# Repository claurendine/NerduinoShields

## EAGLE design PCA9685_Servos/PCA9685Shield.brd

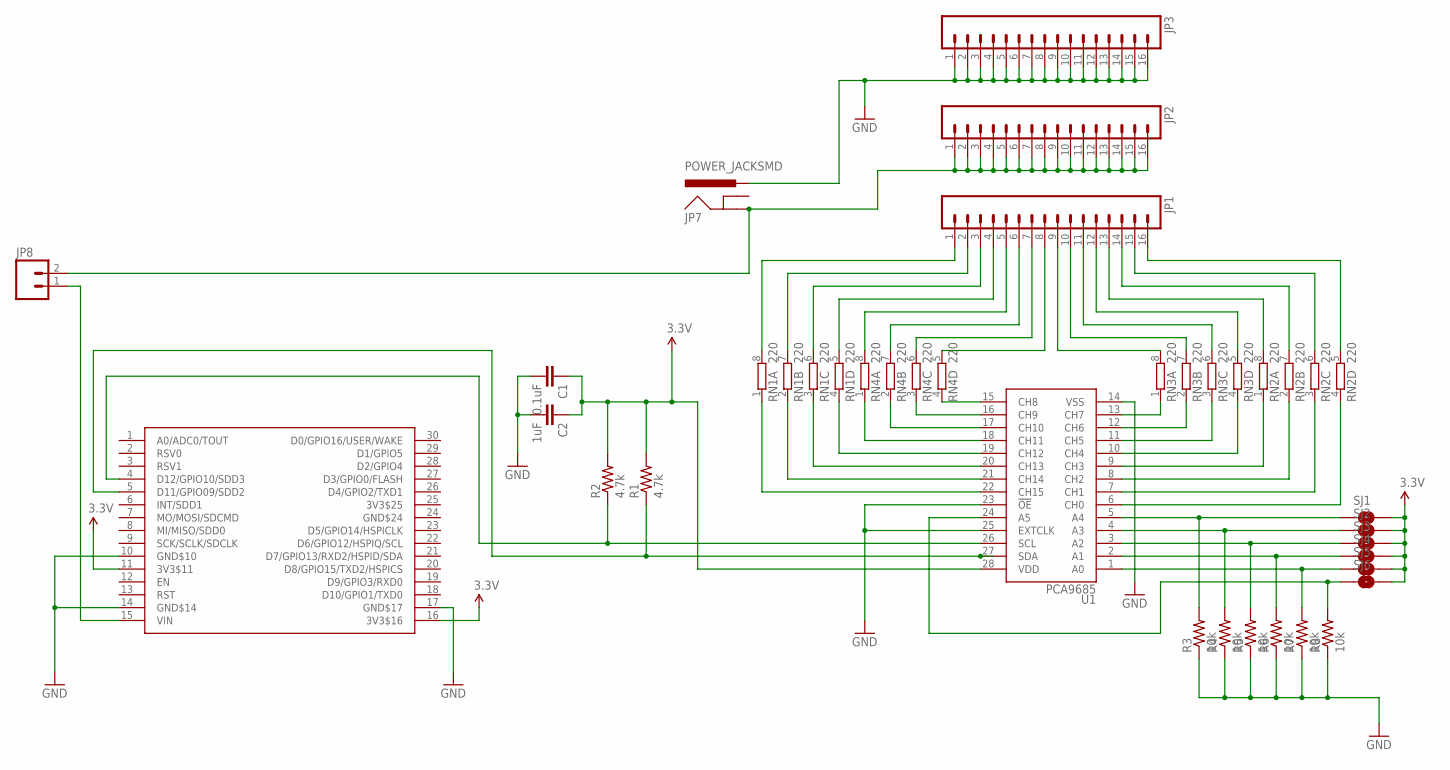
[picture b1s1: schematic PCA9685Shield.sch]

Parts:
C1: 0.1uF; 0402-CAP
C2: 1uF; 0402-CAP
JP1, JP2, JP3: M161X16_NO_SILK; 1X16_NO_SILK
JP7: POWER_JACKSMD; POWER_JACK_SMD
JP8: M021X02_NO_SILK; 1X02_NO_SILK
R1, R2: 4.7k; 0402-RES
R3, R4, R5, R6, R7, R8: 10k; 0402-RES
RN1, RN2, RN3, RN4: 220; EXBS8V
SJ1, SJ2, SJ3, SJ4, SJ5, SJ6: SOLDERJUMPERNO; SJ_2S-NO
U1: PCA9685; TSSOP-28_4MM
U$1: NERDSHIELD; NERDUINO_STACK

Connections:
3.3V: C1.1, C2.1, R1.2, R2.2, SJ1.2, SJ2.2, SJ3.2, SJ4.2, SJ5.2, SJ6.2, U1.28 (VDD), U$1.11 (3V3$11), U$1.16 (3V3$16)
GND: C1.2, C2.2, JP3.1, JP3.2, JP3.3, JP3.4, JP3.5, JP3.6, JP3.7, JP3.8, JP3.9, JP3.10, JP3.11, JP3.12, JP3.13, JP3.14, JP3.15, JP3.16, JP7.VIN0 (PWR), R3.1, R4.1, R5.1, R6.1, R7.1, R8.1, U1.14 (VSS), U1.23 (!OE), U1.25 (EXTCLK), U$1.10 (GND$10), U$1.14 (GND$14), U$1.17 (GND$17)
unnamed: JP8.1, U$1.15 (VIN)
unnamed: R1.1, U1.27 (SDA), U$1.5 (D11/GPIO09/SDD2)
unnamed: R7.2, SJ5.1, U1.1 (A0)
unnamed: R6.2, SJ4.1, U1.2 (A1)
unnamed: R5.2, SJ3.1, U1.3 (A2)
unnamed: R4.2, SJ2.1, U1.4 (A3)
unnamed: R2.1, U1.26 (SCL), U$1.4 (D12/GPIO10/SDD3)
unnamed: R8.2, SJ6.1, U1.24 (A5)
unnamed: RN2.4 (1), U1.6 (CH0)
unnamed: JP1.15, RN2.6 (2)
unnamed: JP1.14, RN2.7 (2)
unnamed: JP1.13, RN2.8 (2)
unnamed: JP1.12, RN3.5 (2)
unnamed: JP1.11, RN3.6 (2)
unnamed: JP1.10, RN3.7 (2)
unnamed: JP1.9, RN3.8 (2)
unnamed: JP1.8, RN4.5 (2)
unnamed: JP1.7, RN4.6 (2)
unnamed: JP1.6, RN4.7 (2)
unnamed: JP1.5, RN4.8 (2)
unnamed: JP1.4, RN1.5 (2)
unnamed: JP1.3, RN1.6 (2)
unnamed: RN1.2 (1), U1.21 (CH14)
unnamed: RN1.1, U1.22 (CH15)
unnamed: JP2.1, JP2.2, JP2.3, JP2.4, JP2.5, JP2.6, JP2.7, JP2.8, JP2.9, JP2.10, JP2.11, JP2.12, JP2.13, JP2.14, JP2.15, JP2.16, JP7.P$4 (GND), JP8.2
unnamed: JP1.2, RN1.7 (2)
unnamed: JP1.1, RN1.8 (2)
unnamed: RN1.3 (1), U1.20 (CH13)
unnamed: RN1.4 (1), U1.19 (CH12)
unnamed: RN4.1, U1.18 (CH11)
unnamed: RN4.2 (1), U1.17 (CH10)
unnamed: RN4.3 (1), U1.16 (CH9)
unnamed: RN4.4 (1), U1.15 (CH8)
unnamed: RN3.1, U1.13 (CH7)
unnamed: RN3.2 (1), U1.12 (CH6)
unnamed: RN3.3 (1), U1.11 (CH5)
unnamed: RN3.4 (1), U1.10 (CH4)
unnamed: RN2.1, U1.9 (CH3)
unnamed: RN2.2 (1), U1.8 (CH2)
unnamed: RN2.3 (1), U1.7 (CH1)
unnamed: JP1.16, RN2.5 (2)
unnamed: R3.2, SJ1.1, U1.5 (A4)

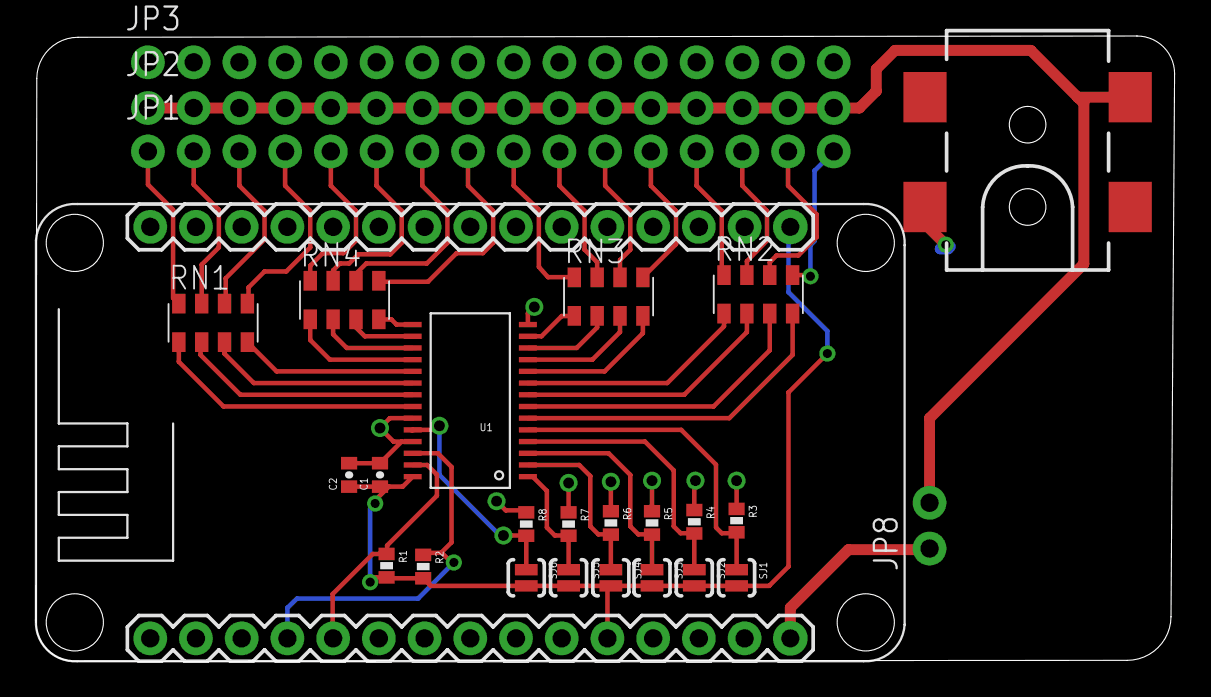
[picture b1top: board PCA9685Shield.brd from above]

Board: 2 copper layers, 63.3 x 34.7 mm, 27 parts (0 on the bottom side), 44 nets.

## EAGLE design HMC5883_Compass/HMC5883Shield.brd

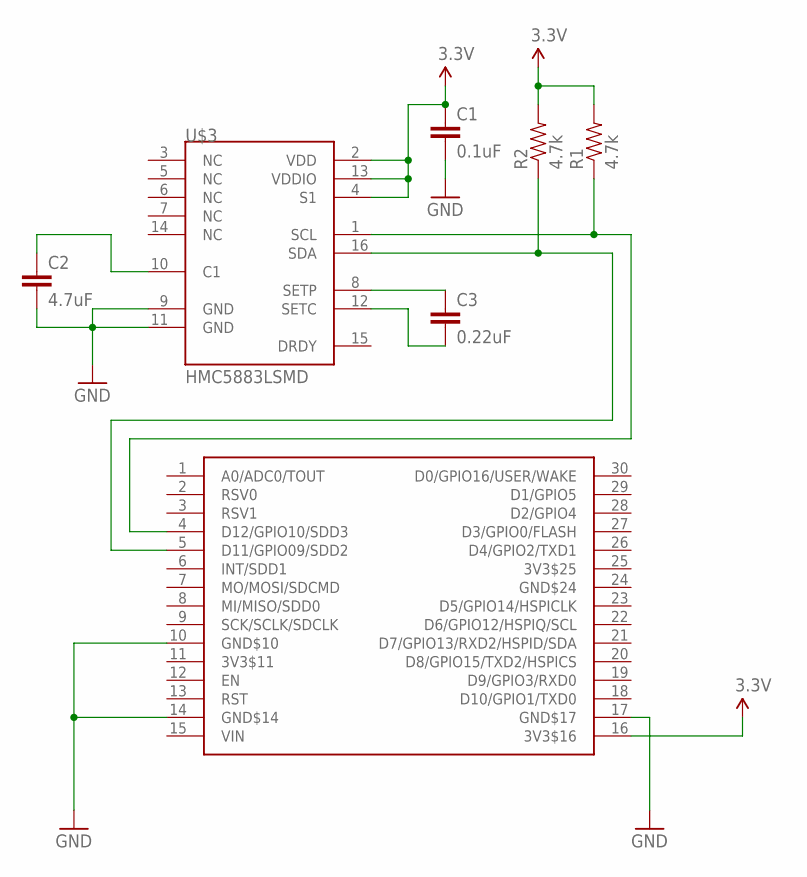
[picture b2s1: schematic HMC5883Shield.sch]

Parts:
C1: 0.1uF; 0402-CAP
C2: 4.7uF; 0402-CAP
C3: 0.22uF; 0402-CAP
R1, R2: 4.7k; 0402-RES
U$1: NERDSHIELD; NERDUINO_STACK
U$3: HMC5883LSMD; 16LPCC

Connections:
3.3V: C1.1, R1.2, R2.2, U$1.16 (3V3$16), U$3.2 (VDD), U$3.4 (S1), U$3.13 (VDDIO)
GND: C1.2, C2.2, U$1.10 (GND$10), U$1.14 (GND$14), U$1.17 (GND$17), U$3.9 (GND), U$3.11 (GND)
unnamed: C2.1, U$3.10 (C1)
unnamed: R2.1, U$1.5 (D11/GPIO09/SDD2), U$3.16 (SDA)
unnamed: R1.1, U$1.4 (D12/GPIO10/SDD3), U$3.1 (SCL)
unnamed: C3.1, U$3.8 (SETP)
unnamed: C3.2, U$3.12 (SETC)

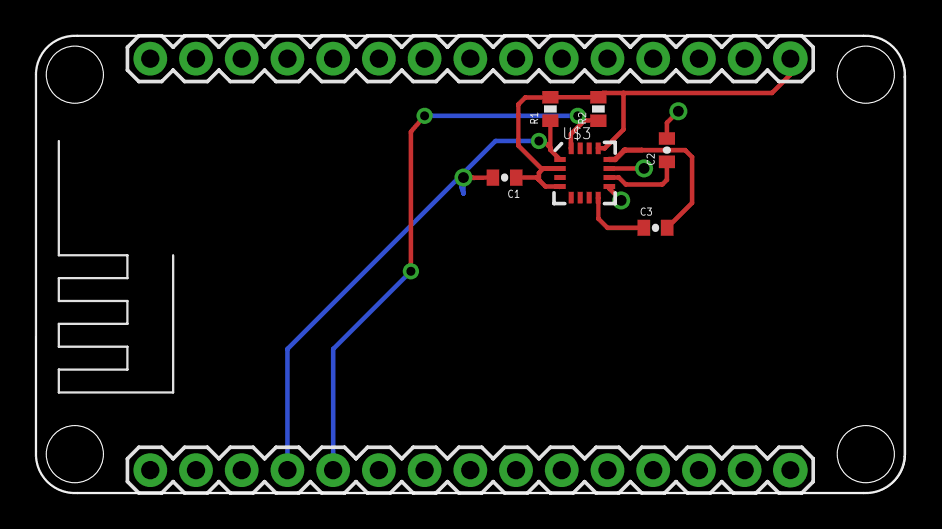
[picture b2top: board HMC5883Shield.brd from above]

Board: 2 copper layers, 48.3 x 25.4 mm, 7 parts (0 on the bottom side), 7 nets.

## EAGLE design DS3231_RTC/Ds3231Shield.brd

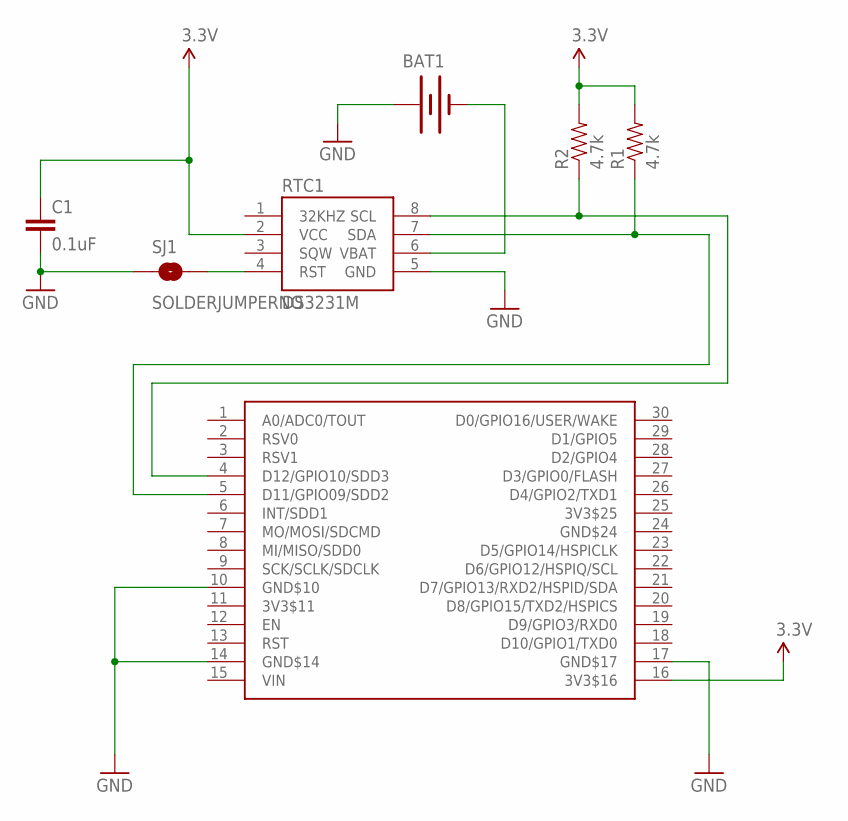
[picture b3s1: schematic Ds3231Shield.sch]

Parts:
BAT1: BATTERY12MM; BATTCON_12MM
C1: 0.1uF; 0402-CAP
R1, R2: 4.7k; 0402-RES
RTC1: DS3231M; SOIC8
SJ1: SOLDERJUMPERNO; SJ_2S-NO
U$1: NERDSHIELD; NERDUINO_STACK

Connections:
3.3V: C1.1, R1.2, R2.2, RTC1.2 (VCC), U$1.16 (3V3$16)
GND: BAT1.PWR@1 (+), C1.2, RTC1.5 (GND), SJ1.1, U$1.10 (GND$10), U$1.14 (GND$14), U$1.17 (GND$17)
unnamed: BAT1.GND (-), RTC1.6 (VBAT)
unnamed: R2.1, RTC1.8 (SCL), U$1.4 (D12/GPIO10/SDD3)
unnamed: R1.1, RTC1.7 (SDA), U$1.5 (D11/GPIO09/SDD2)
unnamed: RTC1.4 (RST), SJ1.2

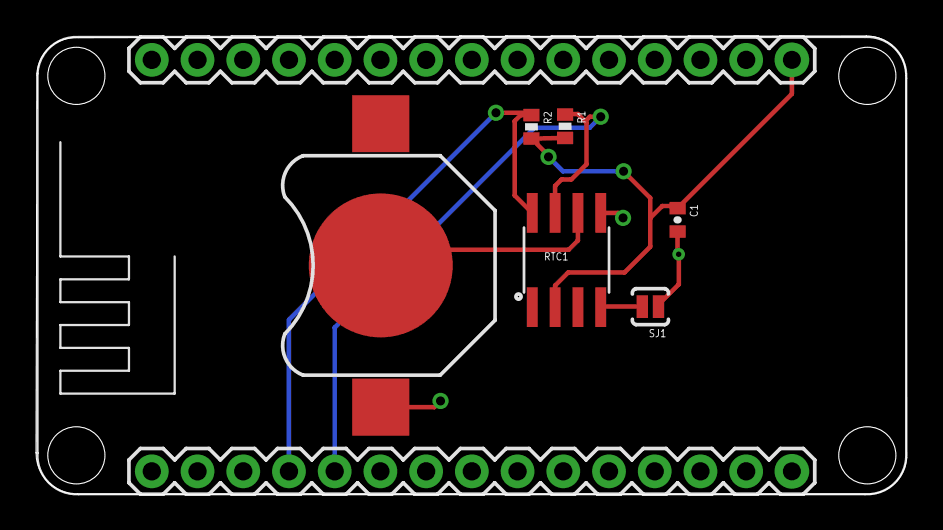
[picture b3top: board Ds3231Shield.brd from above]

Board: 2 copper layers, 48.4 x 25.5 mm, 7 parts (0 on the bottom side), 6 nets.

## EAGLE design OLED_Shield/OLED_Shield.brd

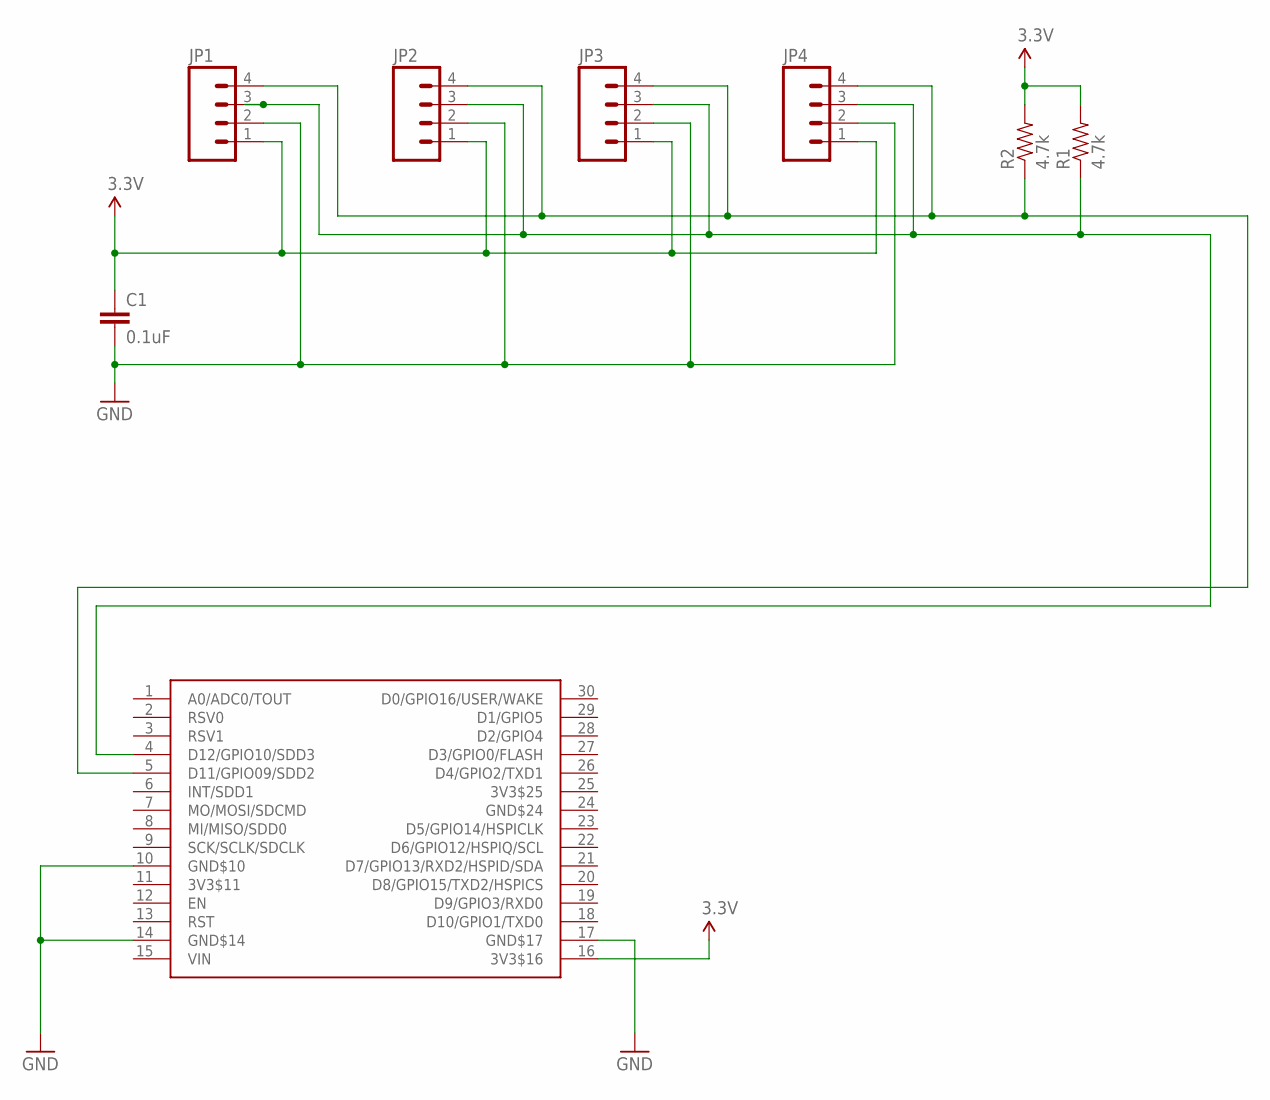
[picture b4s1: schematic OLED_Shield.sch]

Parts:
C1: 0.1uF; 0402-CAP
JP1, JP2, JP3, JP4: M041X04_NO_SILK; 1X04_NO_SILK
R1, R2: 4.7k; 0402-RES
U$1: NERDSHIELD; NERDUINO_STACK

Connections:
3.3V: C1.1, JP1.1, JP2.1, JP3.1, JP4.1, R1.2, R2.2, U$1.16 (3V3$16)
GND: C1.2, JP1.2, JP2.2, JP3.2, JP4.2, U$1.10 (GND$10), U$1.14 (GND$14), U$1.17 (GND$17)
unnamed: JP1.4, JP2.4, JP3.4, JP4.4, R2.1, U$1.5 (D11/GPIO09/SDD2)
unnamed: JP1.3, JP2.3, JP3.3, JP4.3, R1.1, U$1.4 (D12/GPIO10/SDD3)

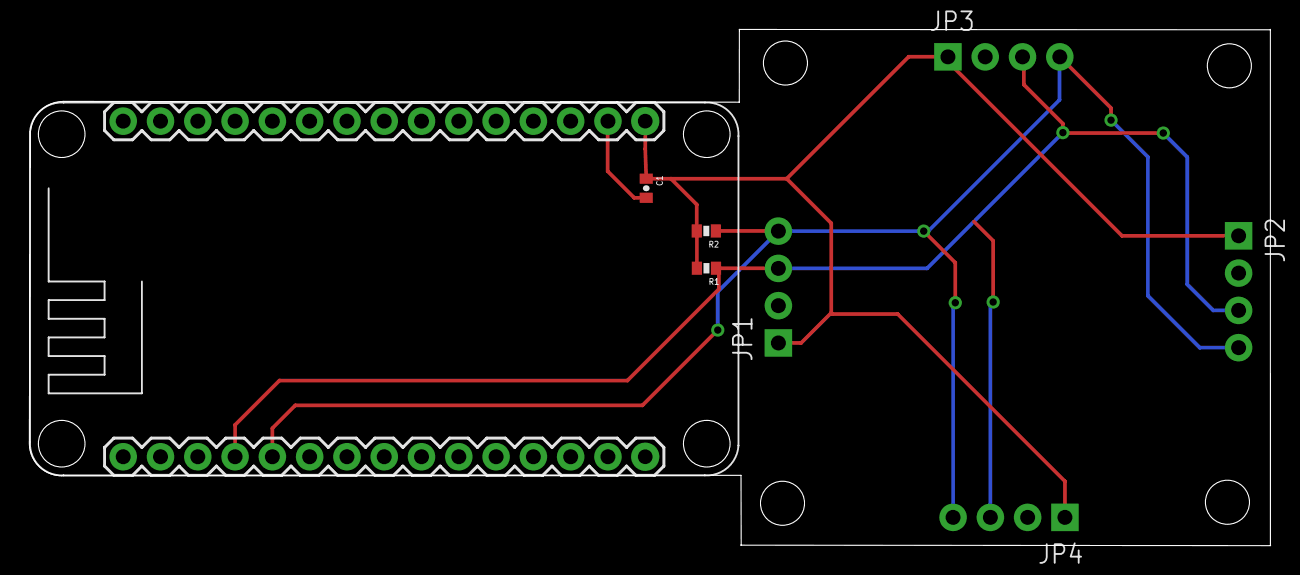
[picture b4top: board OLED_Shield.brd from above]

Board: 2 copper layers, 84.6 x 35.2 mm, 8 parts (0 on the bottom side), 4 nets.

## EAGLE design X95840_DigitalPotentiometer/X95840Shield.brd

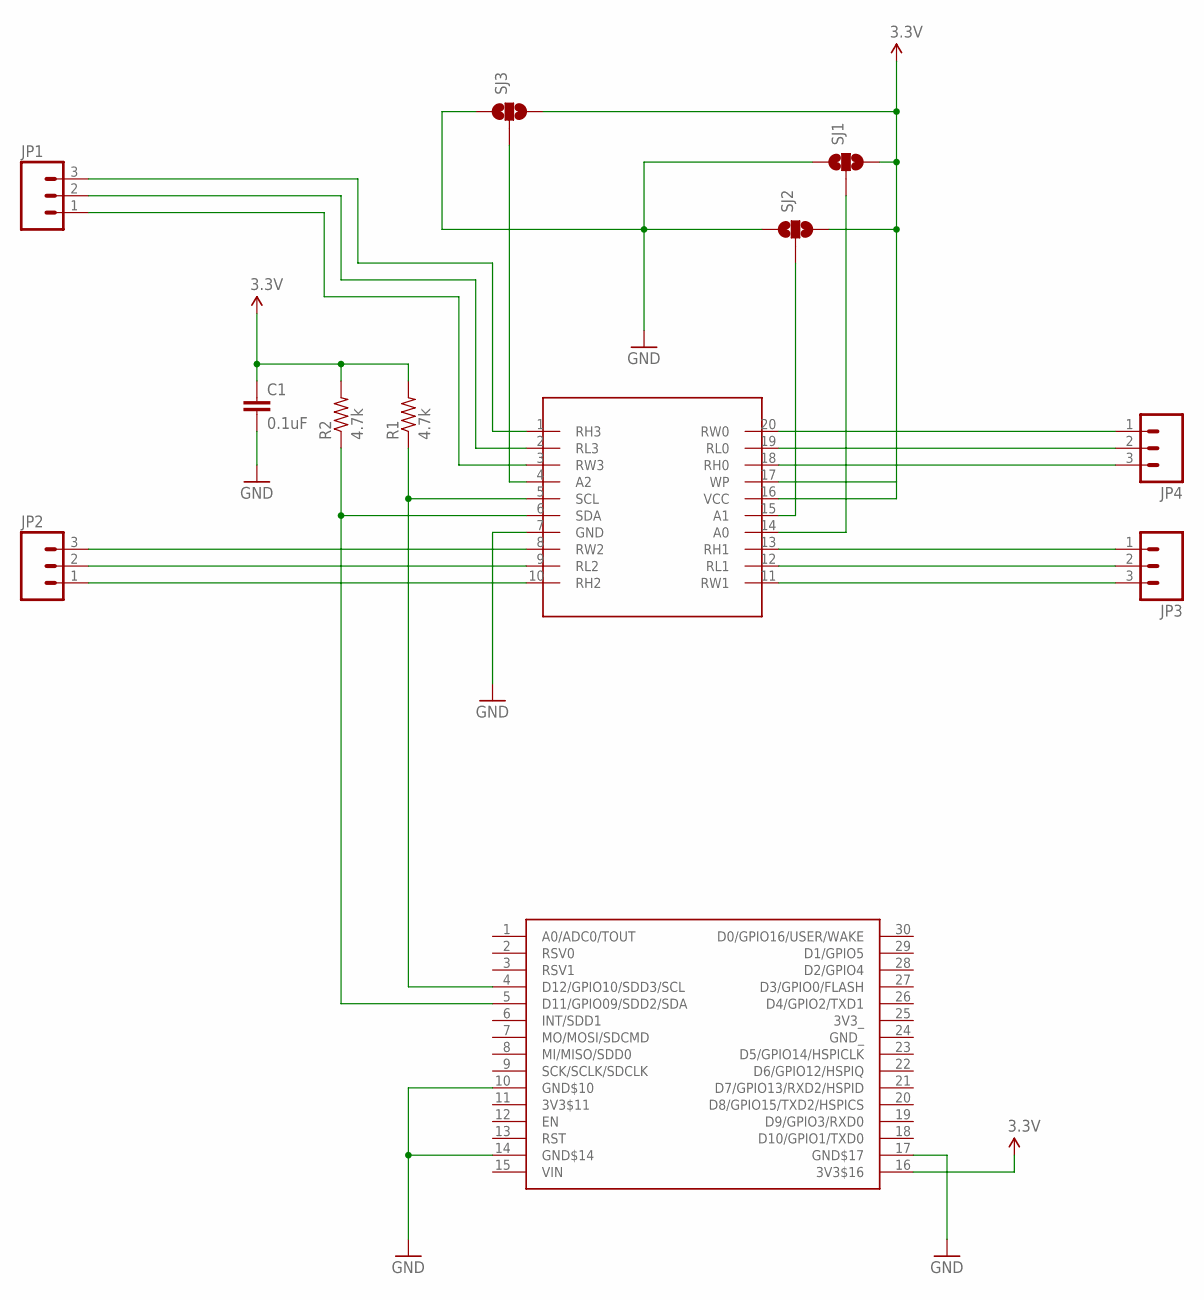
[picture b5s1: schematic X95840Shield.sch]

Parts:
C1: 0.1uF; 0402-CAP
JP1, JP2, JP3, JP4: M03SCREW; SCREWTERMINAL-3.5MM-3
R1, R2: 4.7k; 0402-RES
SJ1, SJ2, SJ3: SOLDERJUMPER_2WAYPASTE1&2; SJ_3_PASTE1&2
U$1: NERDSHIELD; NERDUINO_STACK
U$3: X95840; TSSOP20

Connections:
3.3V: C1.1, R1.2, R2.2, SJ1.3, SJ2.3, SJ3.3, U$1.16 (3V3$16), U$3.16 (VCC), U$3.17 (WP)
GND: C1.2, SJ1.1, SJ2.1, SJ3.1, U$1.10 (GND$10), U$1.14 (GND$14), U$1.17 (GND$17), U$3.7 (GND)
unnamed: SJ3.2, U$3.4 (A2)
unnamed: R2.1, U$1.5 (D11/GPIO09/SDD2/SDA), U$3.6 (SDA)
unnamed: R1.1, U$1.4 (D12/GPIO10/SDD3/SCL), U$3.5 (SCL)
unnamed: JP1.3, U$3.1 (RH3)
unnamed: JP1.2, U$3.2 (RL3)
unnamed: JP1.1, U$3.3 (RW3)
unnamed: JP2.3, U$3.8 (RW2)
unnamed: JP2.2, U$3.9 (RL2)
unnamed: SJ1.2, U$3.14 (A0)
unnamed: SJ2.2, U$3.15 (A1)
unnamed: JP2.1, U$3.10 (RH2)
unnamed: JP3.1, U$3.13 (RH1)
unnamed: JP3.2, U$3.12 (RL1)
unnamed: JP3.3, U$3.11 (RW1)
unnamed: JP4.1, U$3.20 (RW0)
unnamed: JP4.2, U$3.19 (RL0)
unnamed: JP4.3, U$3.18 (RH0)

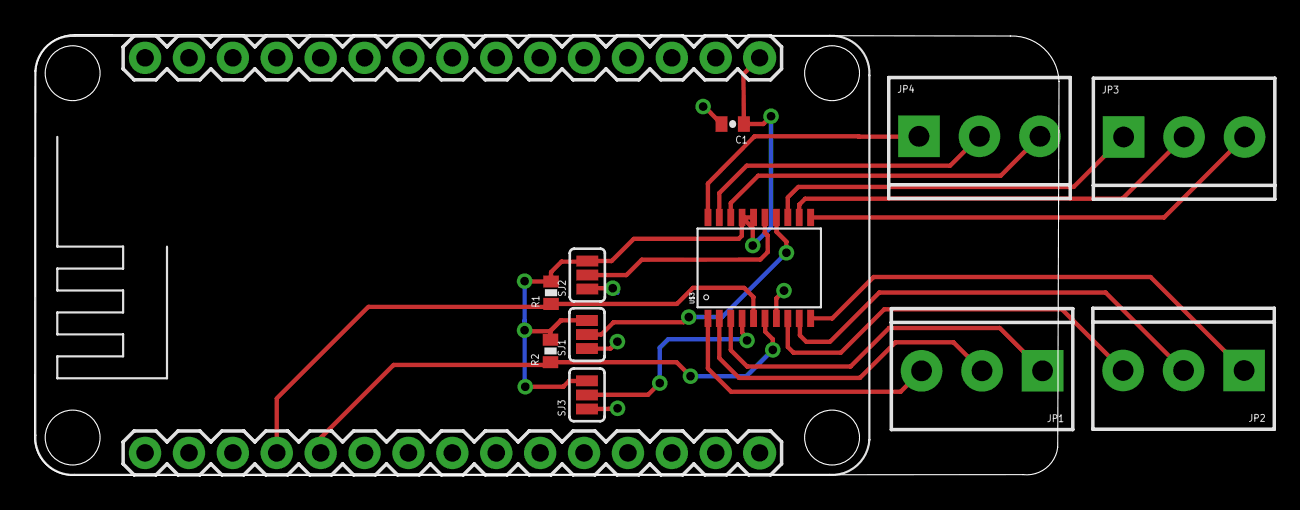
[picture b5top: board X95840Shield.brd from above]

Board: 2 copper layers, 59.3 x 25.5 mm, 12 parts (0 on the bottom side), 19 nets.

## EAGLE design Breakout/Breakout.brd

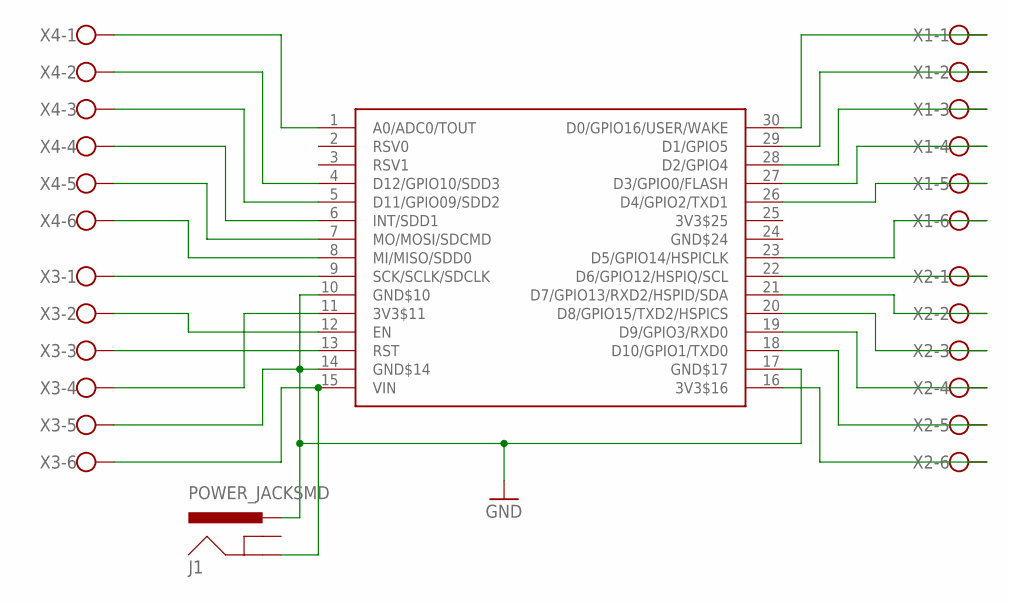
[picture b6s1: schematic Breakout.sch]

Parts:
J1: POWER_JACKSMD; POWER_JACK_SMD
U$1: NERDSHIELD; NERDUINO_STACK
X1, X2, X3, X4: W237-6

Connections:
GND: J1.VIN0 (PWR), U$1.10 (GND$10), U$1.14 (GND$14), U$1.17 (GND$17), X3.5
unnamed: U$1.16 (3V3$16), X2.6
unnamed: U$1.18 (D10/GPIO1/TXD0), X2.5
unnamed: U$1.19 (D9/GPIO3/RXD0), X2.4
unnamed: U$1.20 (D8/GPIO15/TXD2/HSPICS), X2.3
unnamed: U$1.21 (D7/GPIO13/RXD2/HSPID/SDA), X2.2
unnamed: U$1.22 (D6/GPIO12/HSPIQ/SCL), X2.1
unnamed: U$1.23 (D5/GPIO14/HSPICLK), X1.6
unnamed: U$1.26 (D4/GPIO2/TXD1), X1.5
unnamed: U$1.27 (D3/GPIO0/FLASH), X1.4
unnamed: U$1.28 (D2/GPIO4), X1.3
unnamed: U$1.29 (D1/GPIO5), X1.2
unnamed: U$1.30 (D0/GPIO16/USER/WAKE), X1.1
unnamed: U$1.1 (A0/ADC0/TOUT), X4.1
unnamed: U$1.4 (D12/GPIO10/SDD3), X4.2
unnamed: U$1.5 (D11/GPIO09/SDD2), X4.3
unnamed: U$1.6 (INT/SDD1), X4.4
unnamed: U$1.7 (MO/MOSI/SDCMD), X4.5
unnamed: U$1.8 (MI/MISO/SDD0), X4.6
unnamed: U$1.9 (SCK/SCLK/SDCLK), X3.1
unnamed: U$1.12 (EN), X3.2
unnamed: J1.P$4 (GND), U$1.15 (VIN), X3.6
unnamed: U$1.11 (3V3$11), X3.4
unnamed: U$1.13 (RST), X3.3

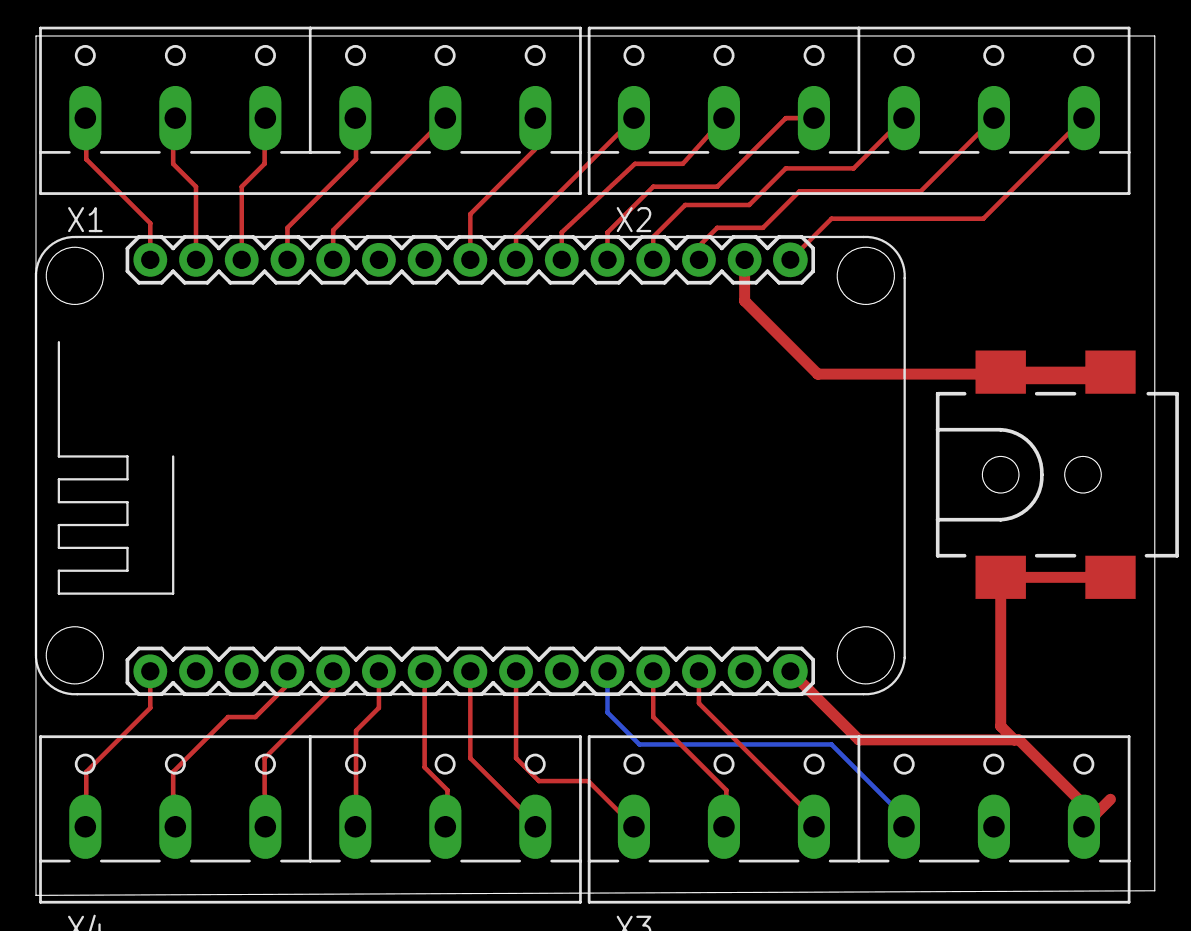
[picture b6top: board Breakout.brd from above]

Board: 2 copper layers, 62.2 x 47.7 mm, 6 parts (0 on the bottom side), 24 nets.

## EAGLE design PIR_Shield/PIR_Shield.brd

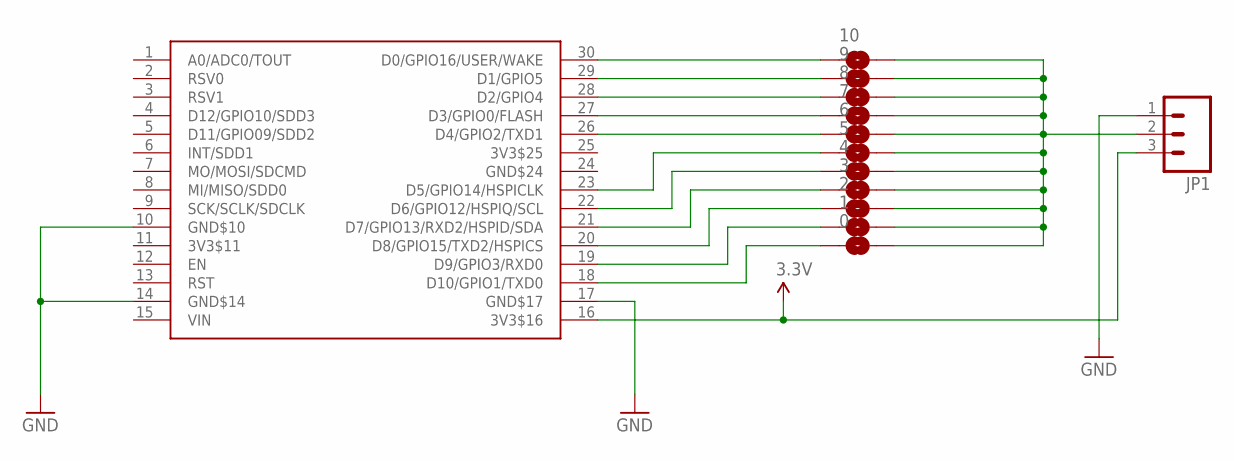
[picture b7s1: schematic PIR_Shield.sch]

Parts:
0, 1, 2, 3, 4, 5, 6, 7, 8, 9: SOLDERJUMPERNO; SJ_2S-NO
10: SOLDERJUMPERNC; SJ_2S
JP1: M03PTH; 1X03
U$1: NERDSHIELD; NERDUINO_STACK

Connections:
3.3V: JP1.3, U$1.16 (3V3$16)
GND: JP1.1, U$1.10 (GND$10), U$1.14 (GND$14), U$1.17 (GND$17)
unnamed: 0.2, 1.2, 2.2, 3.2, 4.2, 5.2, 6.2, 7.2, 8.2, 9.2, 10.2, JP1.2
unnamed: 10.1, U$1.30 (D0/GPIO16/USER/WAKE)
unnamed: 9.1, U$1.29 (D1/GPIO5)
unnamed: 8.1, U$1.28 (D2/GPIO4)
unnamed: 7.1, U$1.27 (D3/GPIO0/FLASH)
unnamed: 6.1, U$1.26 (D4/GPIO2/TXD1)
unnamed: 5.1, U$1.23 (D5/GPIO14/HSPICLK)
unnamed: 4.1, U$1.22 (D6/GPIO12/HSPIQ/SCL)
unnamed: 3.1, U$1.21 (D7/GPIO13/RXD2/HSPID/SDA)
unnamed: 2.1, U$1.20 (D8/GPIO15/TXD2/HSPICS)
unnamed: 1.1, U$1.19 (D9/GPIO3/RXD0)
unnamed: 0.1, U$1.18 (D10/GPIO1/TXD0)

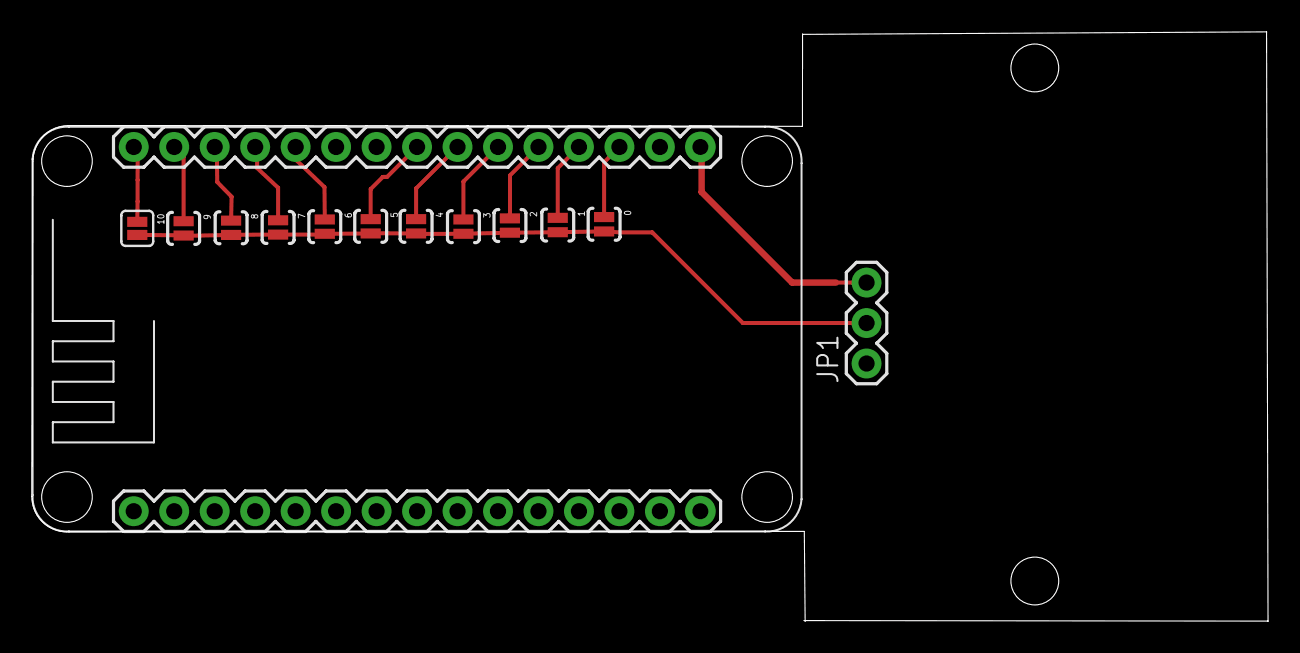
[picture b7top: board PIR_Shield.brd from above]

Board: 2 copper layers, 77.6 x 37.0 mm, 13 parts (0 on the bottom side), 14 nets.

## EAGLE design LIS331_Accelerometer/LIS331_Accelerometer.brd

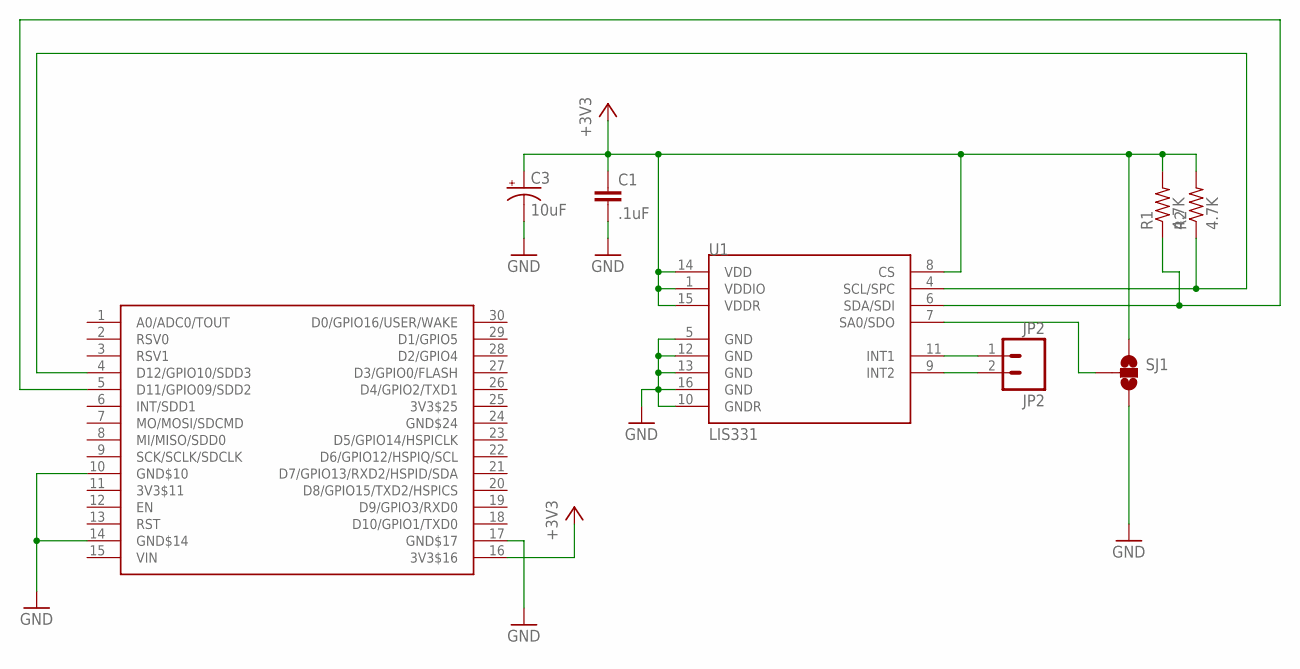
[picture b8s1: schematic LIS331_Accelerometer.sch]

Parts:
C1: .1uF; 0603-CAP
C3: 10uF; EIA3216
JP2: JP2; 1X02
R1, R2: 4.7K; 0603-RES
SJ1: SOLDERJUMPER_2WAYT; SJ_2
U1: LIS331; LGA16-3MM
U$2: NERDSHIELD; NERDUINO_STACK

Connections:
+3V3: C1.1, C3.A (+), R1.2, R2.2, SJ1.1, U1.1 (VDDIO), U1.8 (CS), U1.14 (VDD), U1.15 (VDDR), U$2.16 (3V3$16)
GND: C1.2, C3.C (-), SJ1.3, U1.5 (GND), U1.10 (GNDR), U1.12 (GND), U1.13 (GND), U1.16 (GND), U$2.10 (GND$10), U$2.14 (GND$14), U$2.17 (GND$17)
unnamed: R1.1, U1.6 (SDA/SDI), U$2.5 (D11/GPIO09/SDD2)
unnamed: R2.1, U1.4 (SCL/SPC), U$2.4 (D12/GPIO10/SDD3)
unnamed: SJ1.2, U1.7 (SA0/SDO)
unnamed: JP2.1, U1.11 (INT1)
unnamed: JP2.2, U1.9 (INT2)

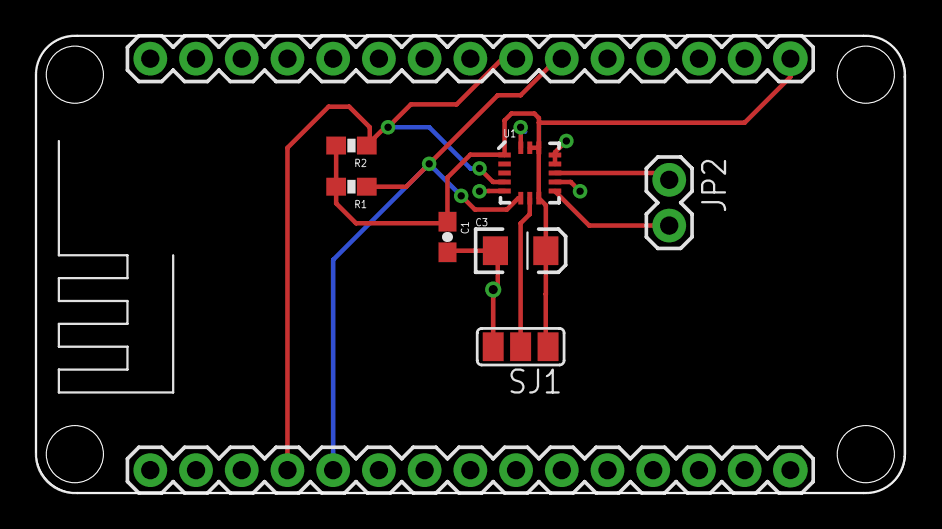
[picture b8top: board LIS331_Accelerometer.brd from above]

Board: 2 copper layers, 48.3 x 25.4 mm, 8 parts (0 on the bottom side), 7 nets.

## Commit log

2015-08-29 Added new shields
2015-08-29 readme
2015-08-29 Added LIS331 accelerometer shield
2015-08-29 Updated stencil text Added PCA9685 and ITG3200 shields
2015-08-30 Added MPR121 shield
2015-09-01 Added lua library
2015-09-01 test
    test
2015-09-01 Updated device address
2015-09-02 Added solder jumpers for address and added resistors to output pins on pca9685 shield Updated labels
2015-09-03 Added BME280 shield
2015-09-09 Updated BMP180 symbol Removed BMP085 shield (redundant) Added DS3231 RTC Shield Added LTC2495 ADC Shield Added chip data sheets for each shield
2015-09-10 Added EEPROM and 16 channel I/O expander shields
2015-09-11 Added NerduinoShieldLib this holds the packaging and symbol definition for the shield
2015-09-11 Updated the shield packaging to include drill holes and profile to match the nodemcu v2 board Applied the updated packaging to the BME280 shield..
2015-09-15 Added OLED Shield Added LiPo Battery Charger Shield Updated outlines of all shields to match the cutout of the nodemcu board
2015-09-16 Added PIR Shield
2015-09-20 Updated the i2c pins to all shields to use d11/d12 as these pins will have dual use with the upcoming wifimcu Added FM24W256 Fram shield Added X95840 Digital potentiometer Shield Added AD5696 DAC Shi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
2015-09-20 Pushed the bme280 adafruit library for reference
2015-09-20 Added bmp085 lua library as reference
2015-09-20 Added adafruit unified sensor library for reference
2015-09-21 Added base I2C shield class for the arduino library Added the BME280 class for the arduino library
2015-09-24 Updated arduino library Added sample arduino sketch to engage all library methods
2015-10-09 Added Nerduino BME280 library

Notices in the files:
parts and their libraries:
SparkFun: Licensing: CC v3.0 Share-Alike You are welcome to use this library for commercial purposes.
SparkFun-DigitalIC: Licensing: Creative Commons ShareAlike 4.0 International - https://creativecommons.org/licenses/by-sa/4.0
